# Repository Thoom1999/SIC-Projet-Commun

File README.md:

# SIC-Projet-Commun
Arduino sensor Project

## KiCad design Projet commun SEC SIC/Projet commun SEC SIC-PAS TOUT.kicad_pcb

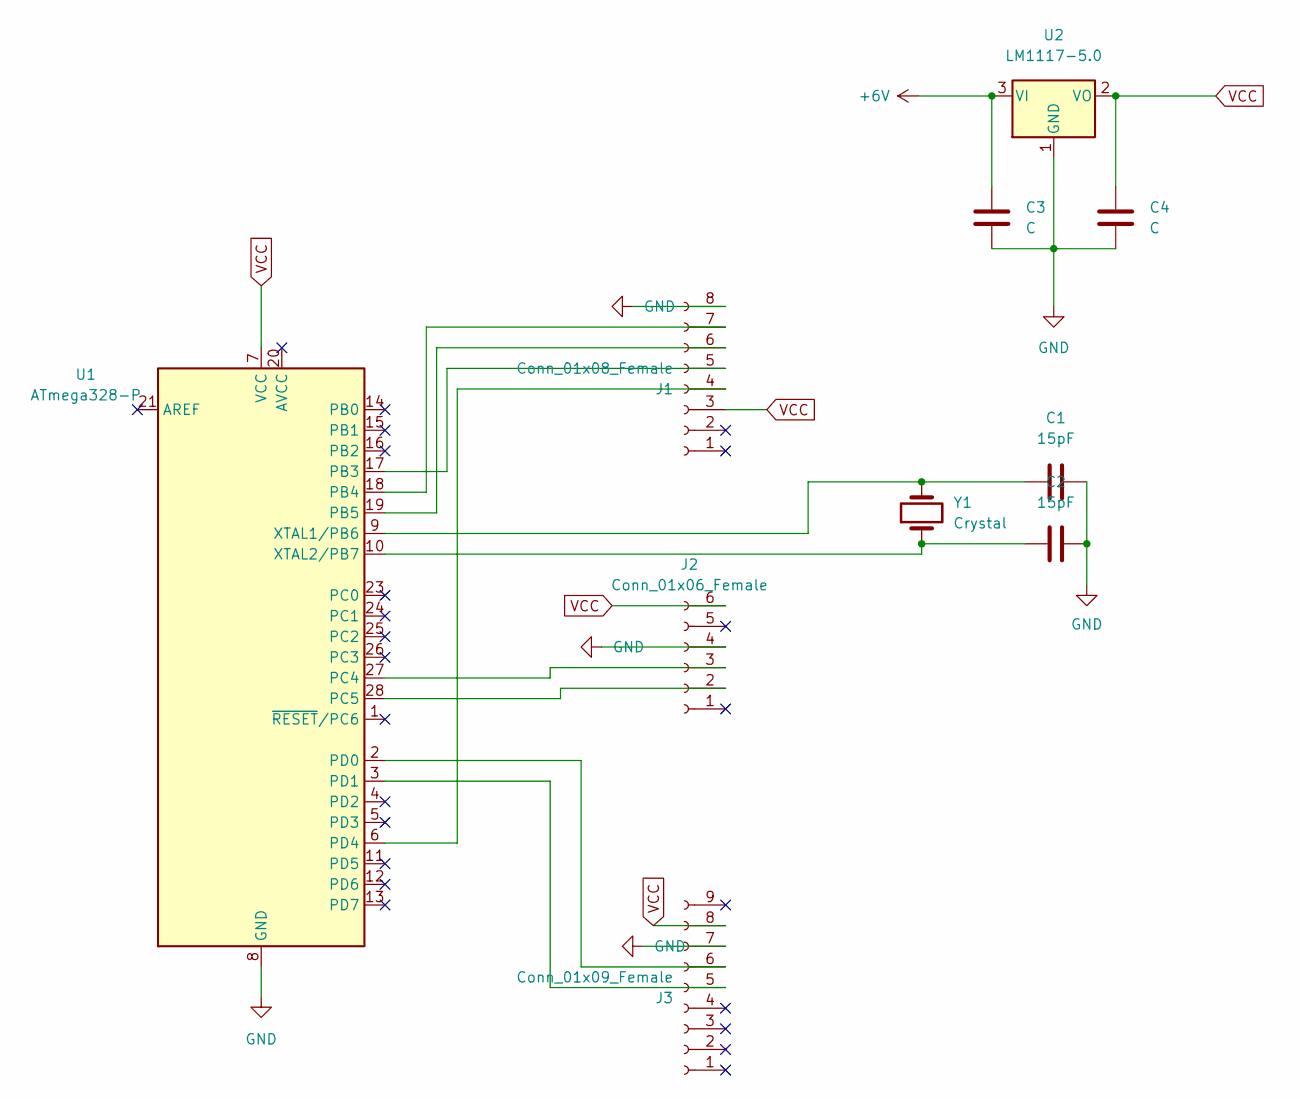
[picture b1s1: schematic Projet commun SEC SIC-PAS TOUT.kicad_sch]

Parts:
C1, C2: 15pF; C_1206_3216Metric
C3, C4: C; C_1206_3216Metric
J1: Conn_01x08_Female; PinSocket_1x08_P2.54mm_Vertical
J2: Conn_01x06_Female; PinSocket_1x06_P2.54mm_Vertical
J3: Conn_01x09_Female; PinSocket_1x09_P2.54mm_Vertical
U1: ATmega328-P; DIP-28_W7.62mm
U2: LM1117-5.0; National_Semiconductor-LM1117IMP-5.0-Level_A
Y1: Crystal; Resonator-2Pin_W10.0mm_H5.0mm

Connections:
+6V: C3.1, U2.3 (VI)
GND: C1.1, C2.1, C3.2, C4.2, J1.8, J2.4, J3.7, U1.8 (GND), U1.22 (GND), U2.1 (GND)
unnamed: C1.2, U1.9 (XTAL1/PB6), Y1.2
unnamed: C2.2, U1.10 (XTAL2/PB7), Y1.1
unnamed: J1.4, U1.6 (PD4)
unnamed: J2.2, U1.28 (PC5)
unnamed: J2.3, U1.27 (PC4)
unnamed: J3.5, U1.3 (PD1)
unnamed: J3.6, U1.2 (PD0)
unnamed: J1.5, U1.17 (PB3)
unnamed: J1.7, U1.18 (PB4)
unnamed: J1.6, U1.19 (PB5)
VCC: C4.1, J1.3, J2.6, J3.8, U1.7 (VCC), U2.2 (VO)

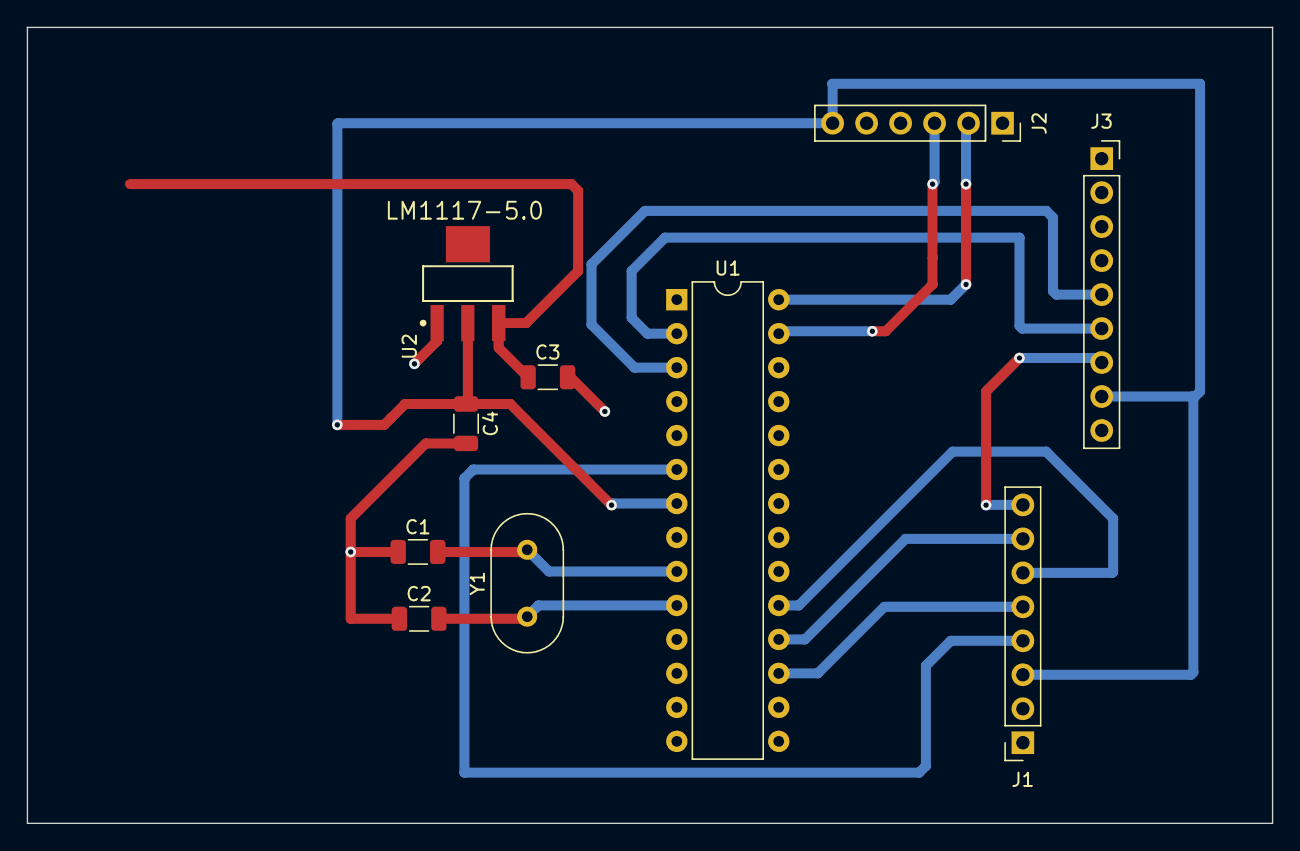
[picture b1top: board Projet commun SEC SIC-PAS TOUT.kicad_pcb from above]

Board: 2 copper layers, 93.1 x 59.5 mm, 10 parts (0 on the bottom side), 13 nets.

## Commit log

2022-12-14 placement elements PCB
2022-12-14 code arduino accéléro & gps
2022-12-14 pcb avec bon pin & quartz & régulateur de tension
2023-01-06 PCB fini
2023-01-06 code arduino
2023-01-09 ceci est un message
